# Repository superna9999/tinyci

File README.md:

# TinyCI

General Concept:

TinyCi Main
-----------

Relay board controlled by a `W32-ETH01` module.

Input: 5V

Produced:
- v0.5: x5 produced, x4 soldered, x3 used in production
- v0.7: x5 produced & used in production
- v0.8: Design done

ESP32 Firmware: see `firmware/tinyci-fw/`

Remote Relay Control script: see `firmware/tinyci-fw/tinyci-relay.py`

TinyCi USB
-----------

Secondary Relay board controlled by the `W32-ETH01` on the main board.

Input: 5V to 12V

Produced:
- v0.1: x5 produced, x3 soldered, x2 used in production
- v0.3: x5 Produced, x0 used in production

TinySerial
-----------

Quad FTDI board + breakout of all FTDI I/Os with the TinyCi form factor + holes
to hook a Pi/LaFrite/LePotato to control the FTDI + TinyCi USBs.

Input: USB

Produced:
- v1: x5 Produced, failed to bringup, will be replaced with OctoSerial using CH348Q

LICENCE
-------

```
CERN OPEN HARDWARE LICENCE v1.1
```

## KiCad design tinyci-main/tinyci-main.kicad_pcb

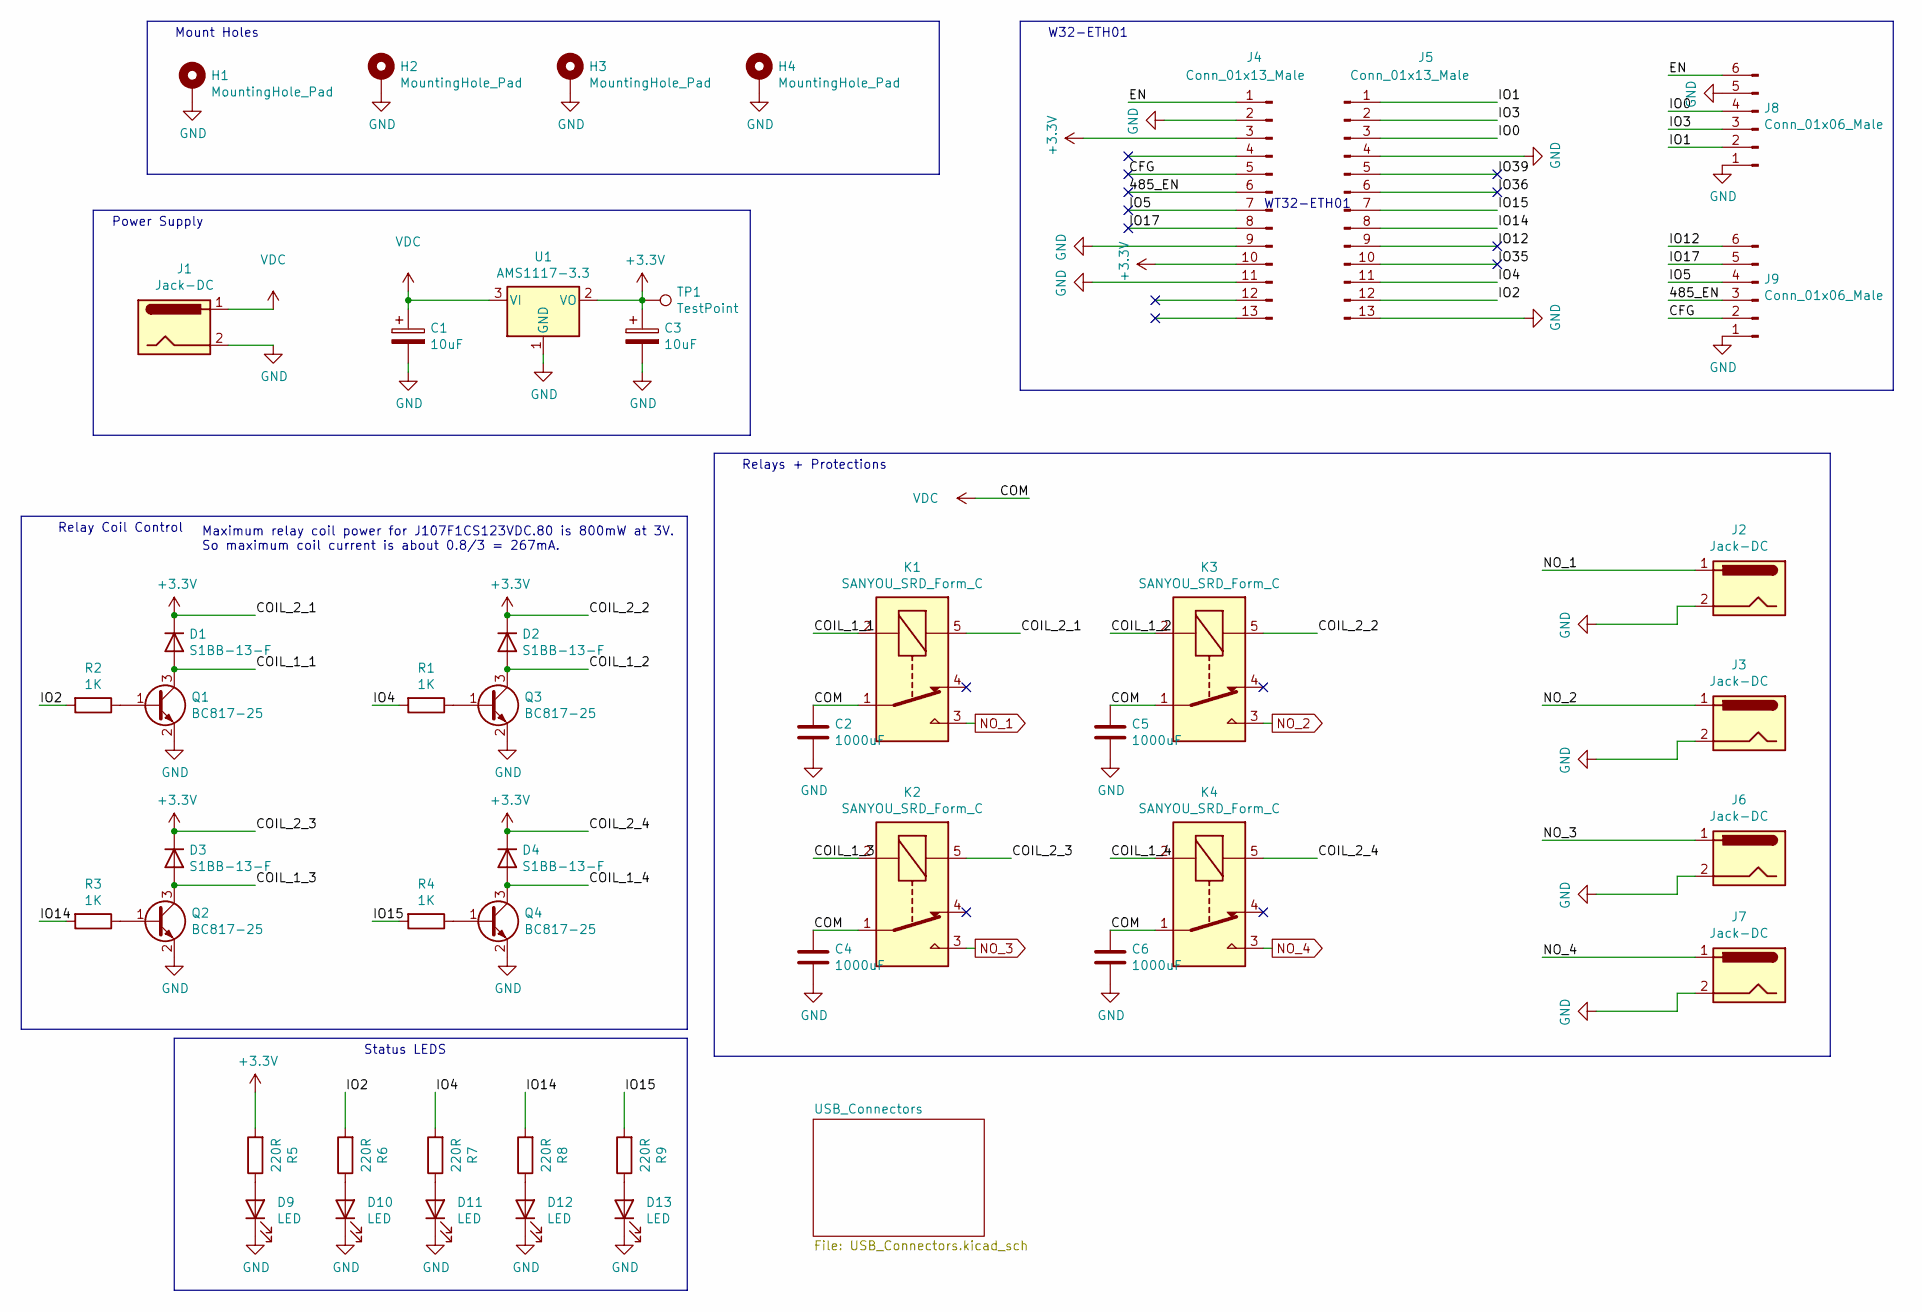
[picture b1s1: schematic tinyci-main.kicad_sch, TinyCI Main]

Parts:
C1, C3: 10uF; CP_EIA-7343-31_Kemet-D
C2, C4, C5, C6: 1000uF; CP_Radial_D10.0mm_P5.00mm
D1, D2, D3, D4: S1BB-13-F; D_SMB_Handsoldering
D9, D10, D11, D12, D13: LED; LED_1206_3216Metric
H1, H2, H3, H4: MountingHole_Pad; MountingHole_3.2mm_M3_Pad
J1, J2, J3, J6, J7: Jack-DC; BarrelJack_Horizontal
J4, J5: Conn_01x13_Male; PinHeader_1x13_P2.54mm_Vertical
J8, J9: Conn_01x06_Male; PinHeader_1x06_P2.54mm_Vertical
K1, K2, K3, K4: SANYOU_SRD_Form_C; Relay_SPDT_SANYOU_SRD_Series_Form_C
Q1, Q2, Q3, Q4: BC817-25; SOT-23
R1, R2, R3, R4: 1K; R_1206_3216Metric
R5, R6, R7, R8, R9: 220R; R_1206_3216Metric
TP1: TestPoint; TestPoint_Pad_D2.0mm
U1: AMS1117-3.3; SOT-223-3_TabPin2

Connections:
+3.3V: C3.1, D1.1 (K), D2.1 (K), D3.1 (K), D4.1 (K), J4.3, J4.10, K1.5, K2.5, K3.5, K4.5, R5.2, TP1.1, U1.2 (VO)
/485_EN: J4.6, J9.3
/CFG: J4.5, J9.2
/COIL_1_1: D1.2 (A), K1.2, Q1.3 (C)
/COIL_1_2: D2.2 (A), K3.2, Q3.3 (C)
/COIL_1_3: D3.2 (A), K2.2, Q2.3 (C)
/COIL_1_4: D4.2 (A), K4.2, Q4.3 (C)
/EN: J4.1, J8.6
/IO0: J5.3, J8.4
/IO1: J5.1, J8.2
/IO2: J5.12, R2.2, R6.2
/IO3: J5.2, J8.3
/IO4: J5.11, R1.2, R7.2
/IO5: J4.7, J9.4
/IO12: J5.9, J9.6
/IO14: J5.8, R3.2, R8.2
/IO15: J5.7, R4.2, R9.2
/IO17: J4.8, J9.5
/IO35: J5.10
/IO36: J5.6
/IO39: J5.5
GND: C1.2, C2.2, C3.2, C4.2, C5.2, C6.2, D9.1 (K), D10.1 (K), D11.1 (K), D12.1 (K), D13.1 (K), H1.1, H2.1, H3.1, H4.1, J1.2, J2.2, J3.2, J4.2, J4.9, J4.11, J5.4, J5.13, J6.2, J7.2, J8.1, J8.5, J9.1, Q1.2 (E), Q2.2 (E), Q3.2 (E), Q4.2 (E), U1.1 (GND); also elsewhere on the board
NO_1: J2.1, K1.3; also elsewhere on the board
NO_2: J3.1, K3.3; also elsewhere on the board
NO_3: J6.1, K2.3; also elsewhere on the board
NO_4: J7.1, K4.3; also elsewhere on the board
unnamed: D9.2 (A), R5.1
unnamed: D10.2 (A), R6.1
unnamed: D11.2 (A), R7.1
unnamed: D12.2 (A), R8.1
unnamed: D13.2 (A), R9.1
unnamed: Q1.1 (B), R2.1
unnamed: Q2.1 (B), R3.1
unnamed: Q3.1 (B), R1.1
unnamed: Q4.1 (B), R4.1
VDC: C1.1, C2.1, C4.1, C5.1, C6.1, J1.1, K1.1, K2.1, K3.1, K4.1, U1.3 (VI)

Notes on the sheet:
Status LEDS
Power Supply
W32-ETH01
Mount Holes
Relays + Protections
Relay Coil Control
WT32-ETH01
Maximum relay coil power for J107F1CS123VDC.80 is 800mW at 3V. So maximum coil current is about 0.8/3 = 267mA.

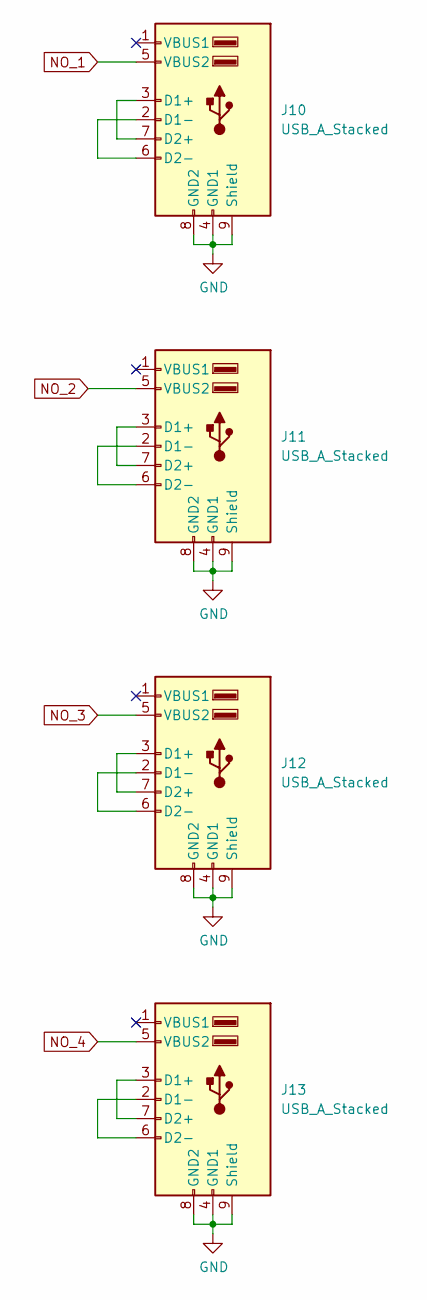
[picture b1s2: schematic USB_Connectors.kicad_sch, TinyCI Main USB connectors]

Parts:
J10, J11, J12, J13: USB_A_Stacked

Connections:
GND: J10.4 (GND1), J10.8 (GND2), J10.9 (Shield), J11.4 (GND1), J11.8 (GND2), J11.9 (Shield), J12.4 (GND1), J12.8 (GND2), J12.9 (Shield), J13.4 (GND1), J13.8 (GND2), J13.9 (Shield); also elsewhere on the board
NO_1: J10.5 (VBUS2); also elsewhere on the board
NO_2: J11.5 (VBUS2); also elsewhere on the board
NO_3: J12.5 (VBUS2); also elsewhere on the board
NO_4: J13.5 (VBUS2); also elsewhere on the board
unnamed: J10.2 (D1-), J10.6 (D2-)
unnamed: J10.3 (D1+), J10.7 (D2+)
unnamed: J11.2 (D1-), J11.6 (D2-)
unnamed: J11.3 (D1+), J11.7 (D2+)
unnamed: J12.2 (D1-), J12.6 (D2-)
unnamed: J12.3 (D1+), J12.7 (D2+)
unnamed: J13.2 (D1-), J13.6 (D2-)
unnamed: J13.3 (D1+), J13.7 (D2+)

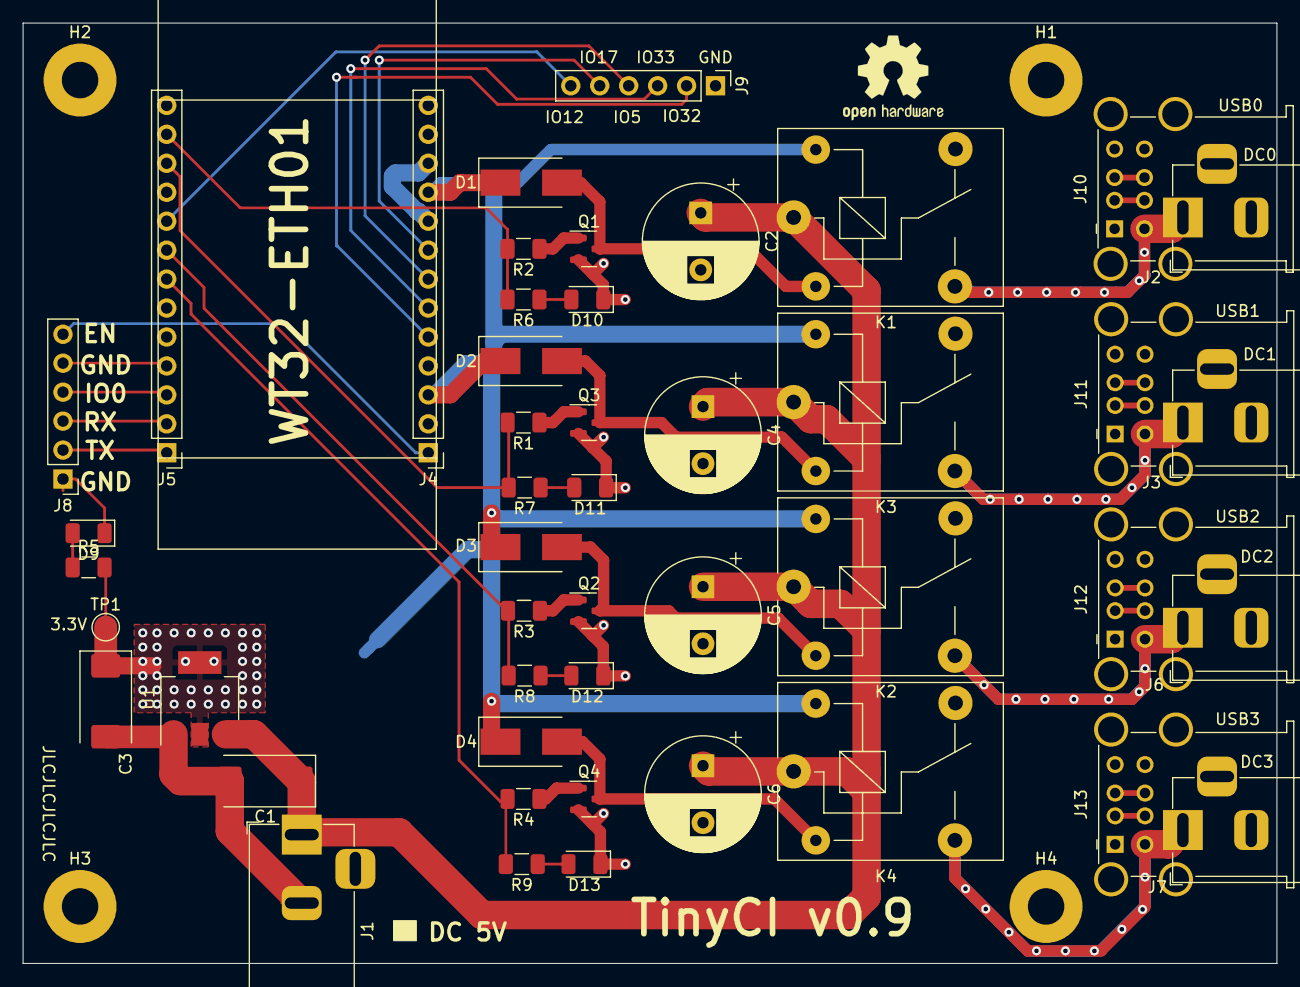
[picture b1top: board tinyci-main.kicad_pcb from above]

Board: 2 copper layers, 110.0 x 82.5 mm, 51 parts (0 on the bottom side), 41 nets.

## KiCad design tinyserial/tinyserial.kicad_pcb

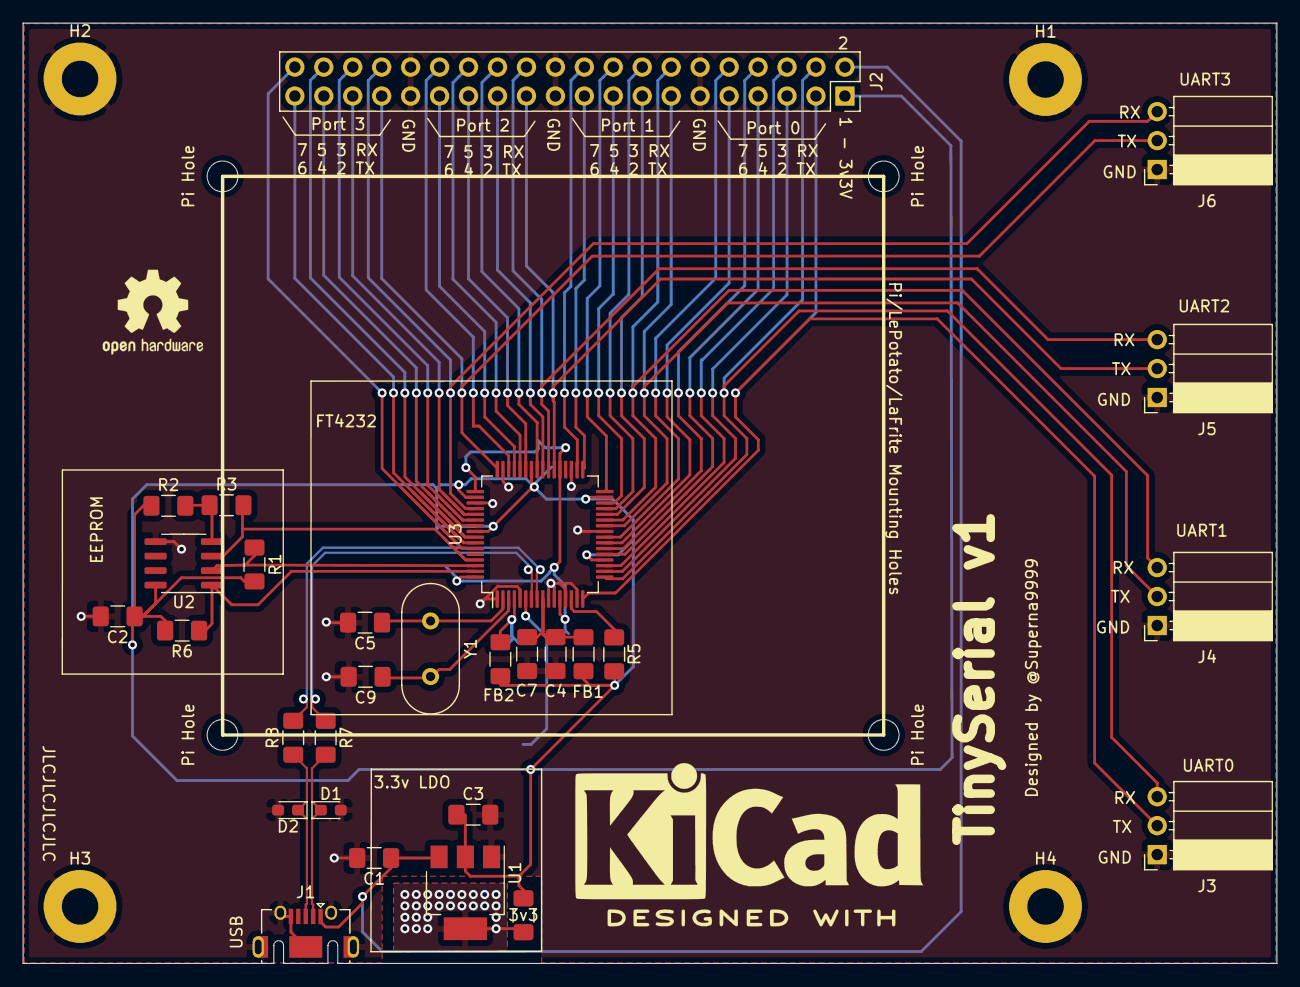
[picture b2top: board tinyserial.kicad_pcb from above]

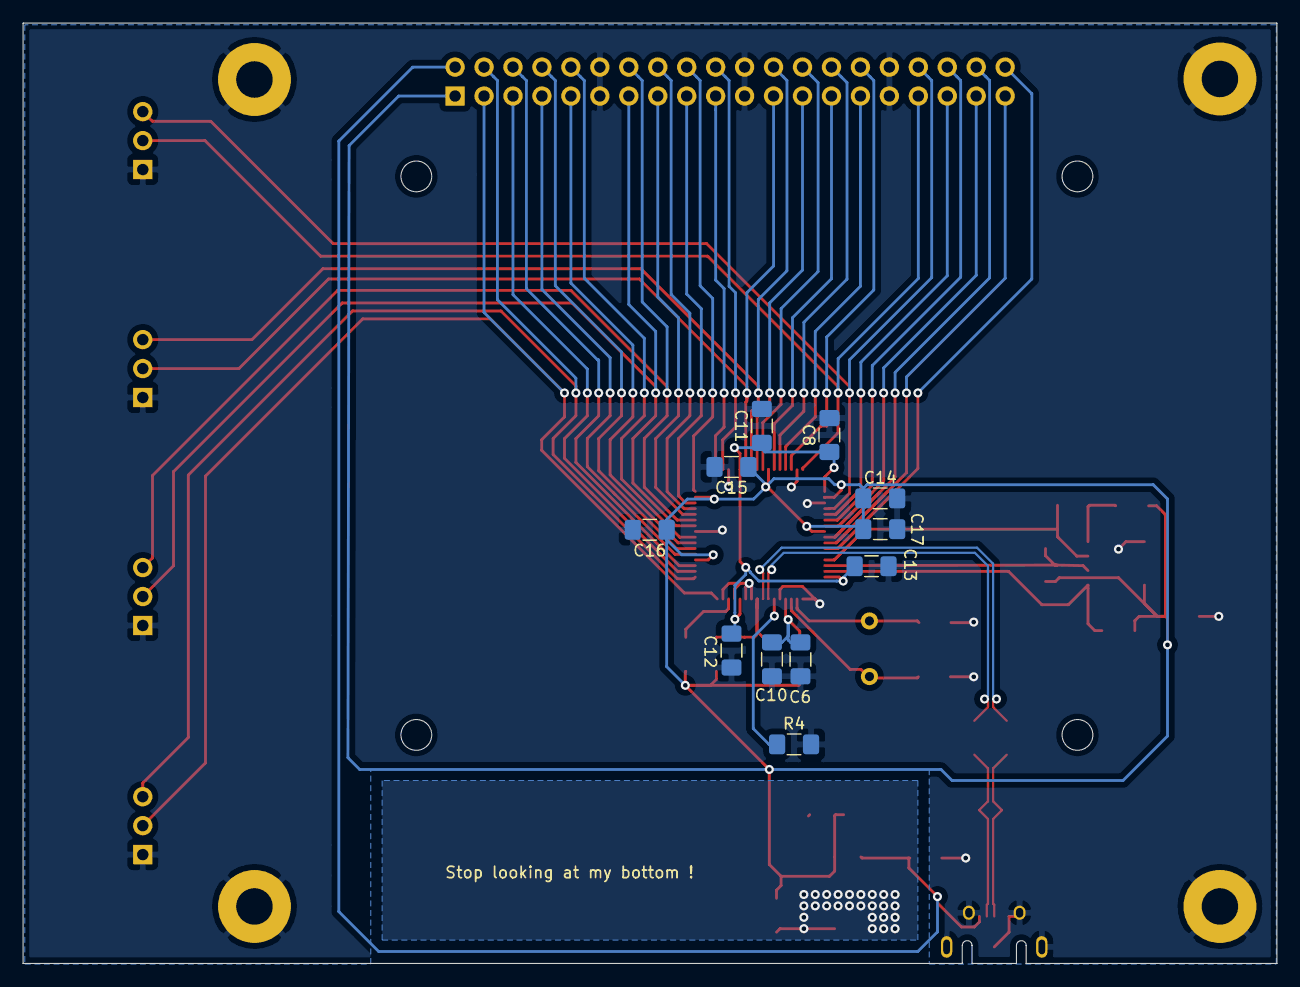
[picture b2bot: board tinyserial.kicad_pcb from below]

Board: 2 copper layers, 110.0 x 82.5 mm, 47 parts (11 on the bottom side), 50 nets.

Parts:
C1, C3: 10uF; C_1206_3216Metric_Pad1.42x1.75mm_HandSolder
C2, C7, C8, C10, C11, C12, C13, C14, C15, C16, C17: 100nF; C_1206_3216Metric_Pad1.42x1.75mm_HandSolder
C4, C6: 4.7uF; C_1206_3216Metric_Pad1.42x1.75mm_HandSolder
C5, C9: 30pF; C_1206_3216Metric_Pad1.42x1.75mm_HandSolder
D1, D2: D_TVS; D_0603_1608Metric_Pad1.05x0.95mm_HandSolder
FB1, FB2: Ferrite_Bead; R_1206_3216Metric_Pad1.42x1.75mm_HandSolder
H1, H2, H3, H4: MountingHole_Pad; MountingHole_3.2mm_M3_Pad
J1: USB_OTG; USB_Micro-AB_Molex_47590-0001
J2: Conn_02x20_Odd_Even; PinSocket_2x20_P2.54mm_Vertical
J3, J4, J5, J6: Conn_01x03_Male; PinSocket_1x03_P2.54mm_Horizontal
Pi Hole: MountingHole_2.7mm_M2.5
Pi Hole#2, Pi Hole#3, Pi Hole#4: MountingHole_2.7mm_M2.5
R1, R2, R6, R7, R8: 10K; R_1206_3216Metric_Pad1.42x1.75mm_HandSolder
R3: 2.2K; R_1206_3216Metric_Pad1.42x1.75mm_HandSolder
R4: 12K/1%; R_1206_3216Metric_Pad1.42x1.75mm_HandSolder
R5: 1K; R_1206_3216Metric_Pad1.42x1.75mm_HandSolder
U1: AMS1117-3.3; SOT-223-3_TabPin2
U2: 93LC46B/SN; SOIC-8_3.9x4.9mm_P1.27mm
U3: FT4232HL; LQFP-64_10x10mm_P0.5mm
Y1: 12MHz; Crystal_HC49-4H_Vertical

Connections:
+1V8: C8.1, C11.1, C12.1, C13.1, U3.12, U3.37, U3.49, U3.64
+3V3: C2.1, C3.1, C14.1, C15.1, C16.1, C17.1, FB1.2, FB2.2, J2.1, R1.2, R2.1, R5.1, R6.2, U1.2, U2.8, U3.20, U3.31, U3.42, U3.50, U3.56
/A2: J2.5, U3.18
/A3: J2.6, U3.19
/A4: J2.7, U3.21
/A5: J2.8, U3.22
/A6: J2.9, U3.23
/A7: J2.10, U3.24
/B2: J2.15, U3.28
/B3: J2.16, U3.29
/B4: J2.17, U3.30
/B5: J2.18, U3.32
/B6: J2.19, U3.33
/B7: J2.20, U3.34
/C2: J2.25, U3.40
/C3: J2.26, U3.41
/C4: J2.27, U3.43
/C5: J2.28, U3.44
/C6: J2.29, U3.45
/C7: J2.30, U3.46
/D2: J2.35, U3.53
/D3: J2.36, U3.54
/D4: J2.37, U3.55
/D5: J2.38, U3.57
/D6: J2.39, U3.58
/D7: J2.40, U3.59
/D+: D2.1, J1.3, R8.1
/D-: D1.1, J1.2, R7.2
/EECLK: R1.1, U2.2, U3.62
/EECS: R6.1, U2.1, U3.63
/EEDATA: R3.2, U2.3, U3.61
/FD+: R8.2, U3.8
/FD-: R7.1, U3.7
/RX0: J2.4, J3.3, U3.17
/RX1: J2.14, J4.3, U3.27
/RX2: J2.24, J5.3, U3.39
/RX3: J2.34, J6.3, U3.52
/TX0: J2.3, J3.2, U3.16
/TX1: J2.13, J4.2, U3.26
/TX2: J2.23, J5.2, U3.38
/TX3: J2.33, J6.2, U3.48
GND: C1.2, C2.2, C3.2, C4.2, C5.2, C6.2, C7.2, C8.2, C9.2, C10.2, C11.2, C12.2, C13.2, C14.2, C15.2, C16.2, C17.2, D1.2, D2.2, H1.1, H2.1, H3.1, H4.1, J1.5, J1.6, J2.11, J2.12, J2.21, J2.22, J2.31, J2.32, J3.1, J4.1, J5.1, J6.1, R4.2, U1.1, U2.5, U3.1, U3.5, U3.10, U3.11, U3.13, U3.15, U3.25, U3.35, U3.47, U3.51
unnamed: C4.1, C7.1, FB1.1, U3.9
unnamed: C5.1, U3.2, Y1.1
unnamed: C9.1, U3.3, Y1.2
unnamed: C6.1, C10.1, FB2.1, U3.4
unnamed: R2.2, R3.1, U2.4
unnamed: R4.1, U3.6
unnamed: R5.2, U3.14
VBUS: C1.1, J1.1, J2.2, U1.3

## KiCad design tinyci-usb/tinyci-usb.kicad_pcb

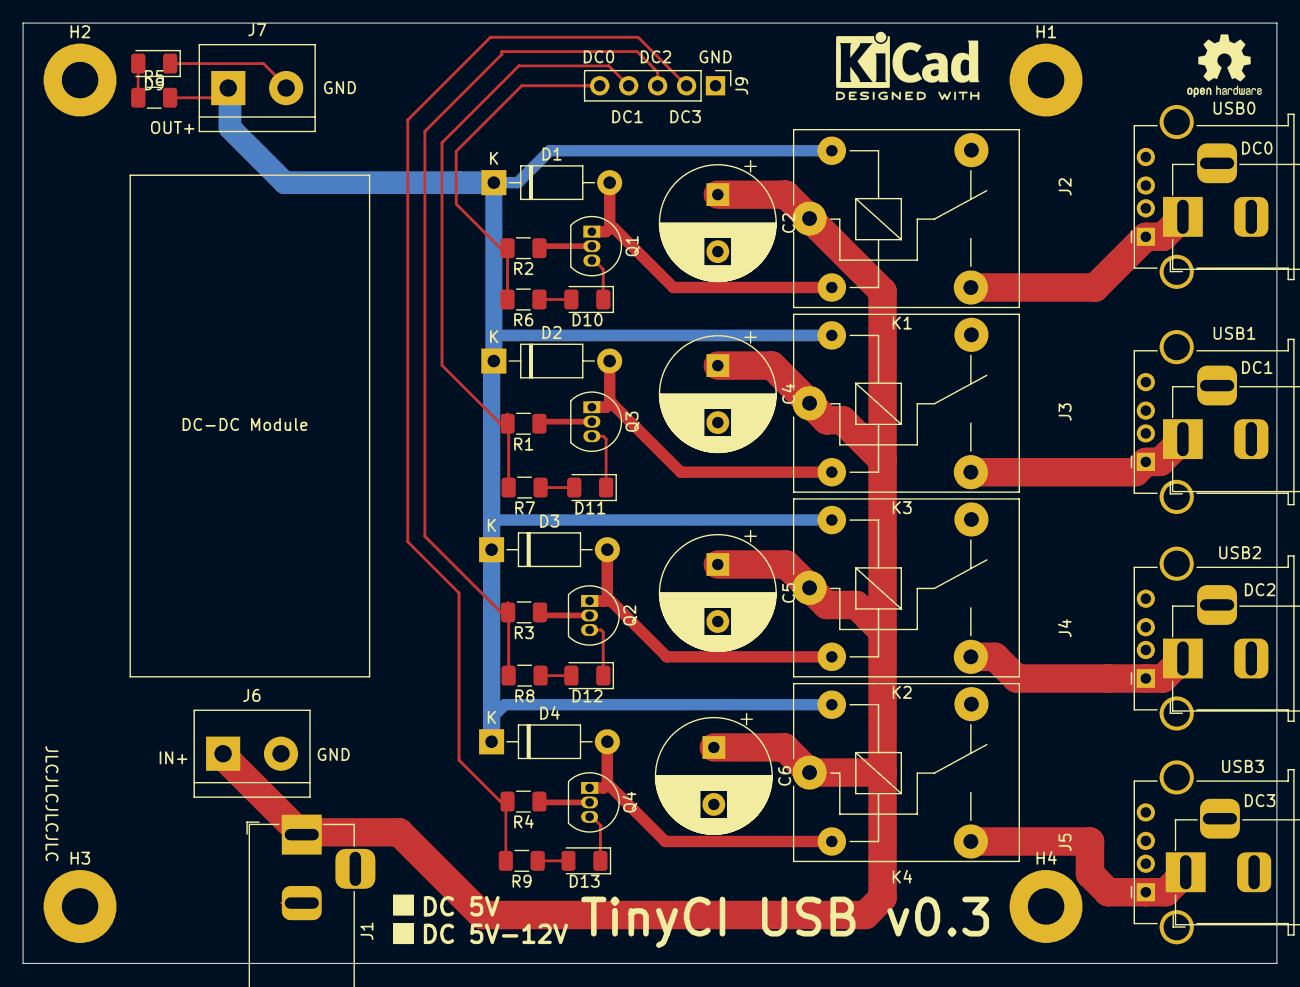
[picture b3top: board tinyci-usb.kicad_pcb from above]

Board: 2 copper layers, 110.0 x 82.5 mm, 46 parts (0 on the bottom side), 24 nets.

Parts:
C2, C4, C5, C6: 1000uF; CP_Radial_D10.0mm_P5.00mm
D1, D2, D3, D4: 1N4001; D_DO-41_SOD81_P10.16mm_Horizontal
D9, D10, D11, D12, D13: LED; LED_1206_3216Metric
H1, H2, H3, H4: MountingHole_Pad; MountingHole_3.2mm_M3_Pad
J1: Jack-DC; BarrelJack_Horizontal
J2, J3, J4, J5: USB_A; USB_A_Stewart_SS-52100-001_Horizontal
J6, J7: Screw_Terminal_01x02; TerminalBlock_bornier-2_P5.08mm
J9: Conn_01x04_Male; PinHeader_1x05_P2.54mm_Vertical
K1, K2, K3, K4: SANYOU_SRD_Form_C; Relay_SPDT_SANYOU_SRD_Series_Form_C
Q1, Q2, Q3, Q4: BC337; TO-92_Inline
R1, R2, R3, R4: 1K; R_1206_3216Metric
R5, R6, R7, R8, R9: 220R; R_1206_3216Metric
USB0, USB1, USB2, USB3: BarrelJack_Horizontal

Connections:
+3V3: D1.1, D2.1, D3.1, D4.1, J7.1, K1.5, K2.5, K3.5, K4.5, R5.2
+VDC: C2.1, C4.1, C5.1, C6.1, J1.1, J6.1, K1.1, K2.1, K3.1, K4.1
/COIL_1_1: D1.2, K1.2, Q1.1
/COIL_1_2: D2.2, K3.2, Q3.1
/COIL_1_3: D3.2, K2.2, Q2.1
/COIL_1_4: D4.2, K4.2, Q4.1
/NO_1: J2.1, K1.3, USB0.1
/NO_2: J3.1, K3.3, USB1.1
/NO_3: J4.1, K2.3, USB2.1
/NO_4: J5.1, K4.3, USB3.1
/RELAY1: J9.5, R2.2, R6.2
/RELAY2: J9.4, R1.2, R7.2
/RELAY3: J9.3, R3.2, R8.2
/RELAY4: J9.2, R4.2, R9.2
GND: C2.2, C4.2, C5.2, C6.2, D9.1, D10.1, D11.1, D12.1, D13.1, H1.1, H2.1, H3.1, H4.1, J1.2, J2.4, J2.5, J3.4, J3.5, J4.4, J4.5, J5.4, J5.5, J6.2, J7.2, J9.1, Q1.3, Q2.3, Q3.3, Q4.3, USB0.2, USB1.2, USB2.2, USB3.2
unnamed: D9.2, R5.1
unnamed: D10.2, R6.1
unnamed: D11.2, R7.1
unnamed: D12.2, R8.1
unnamed: D13.2, R9.1
unnamed: Q1.2, R2.1
unnamed: Q2.2, R3.1
unnamed: Q3.2, R1.1
unnamed: Q4.2, R4.1

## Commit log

2020-11-18 Add v0.4 of tinicy-main and v0.1 of tiny-usb
2020-11-18 Specify Licence
2020-11-18 fixup! Specify Licence
2020-11-18 Version v0.5
2020-11-18 fixup! Version v0.5
2020-11-18 fixup! fixup! Version v0.5
2020-11-18 TinyCI USB v0.1
2020-11-18 Add README and pictures
2020-11-18 fixup! Add README and pictures
2020-11-18 Fixup gitignore
2020-11-18 Add LICENCE to TinyCI-main
2020-11-18 Add LICENCE to TinyCI-USB
2020-11-23 Update prices with aliexpress commands & refs
2020-12-01 Ordered Version !
2020-12-02 Initial version of UDP controlled WT32-ETH01 firmware
2020-12-02 Add UDP command parsing to toggle GPIOs
2021-01-08 TinyCI USB 0.2
    - Updated schematic with correct USB Type A footprint
    - Fixed bad relay output (outputs must be disabled by default, activating the relay will send power to outputs)
    - removed LDO
    - added DC-DC screw terminal footprint + drawing of LM2596 DC-DC module to solder
    - grow mounting hole to 3.2mm to target M3 screws
    - relay 4 was missing Vinput signal to pin 1
2021-01-08 TinyCI 0.6
    - Fixed bad relay output (outputs must be disabled by default, activating the relay will send power to outputs)
    - grow mounting hole to 3.2mm to target M3 screws
    - removed "5v-12v" text, this board will be 5V only, LDO heats too much at 12V
2021-09-03 Add tinyci-relay.py
2021-09-03 Fixup tinyci-relay.py for python3
2021-11-19 TinyCI Main v0.7
    Remove post-relay protections, and move 1000uF caps before relay.
    Add proper OSHW & Made with KiCad logo
2021-11-19 TinyCI USB 0.3
    Remove post-relay protections, and move 1000uF caps before relay.
    Add proper OSHW & Made with KiCad logo
2021-11-19 Introduce TinySerial v1
    FT4232 quad uart board with 40pin header for all I/Os
    with same form factor as TinyCI.
    Also has holes to hook a Pi/LaFrite/LePotato to control the board
    and eventually some TinyCi USB relays.
2022-11-11 firmware: tinyci-relay: remove unused import
    Some import are useless, remove them.
2022-11-11 firmware: tinyci-relay: add a shebang
    Add missing shebang
2022-12-01 tinyci-main: Converted project and schematic to KiCad 6.
    Had to replace C1 and C3 capacitors symbol because it has been renamed in KiCad 6.
2022-12-01 tinyci-main: Converted PCB to KiCad 6.
2022-12-01 tinyci-main: Added stacked USB-A connectors to schematic so they are easier to route.
2022-12-01 tinyci-main: Replaced the PCB single USB-A connectors by the stacked ones.
2022-12-02 tinyci-main: Bumped version to 0.8.
2022-12-02 Update README for TinySerial
2023-01-09 tinyci-relay: need to import sys
    My cleaning via f256e9216f3e ("firmware: tinyci-relay: remove unused import") was too much, I removed sys when I should not.
2023-01-09 convert to new API
    esp_eth_set_default_handlers was removed, so let's convert to new API.
2023-01-09 implement version
    Add a simple VERSION command returning build version
2023-02-15 tinyci-main: Replaced the relay coil flyback diodes by SMD parts to speed up the board assembly.
2023-02-15 tinyci-main: Replaced the relay coil transistors by SMD parts to speed up the board assembly.
2023-02-15 tinyci-main: Bumped version to 0.9.

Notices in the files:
tinyci-main/USB_Connectors.kicad_sch:
Copyright (C) 2021 Neil Armstrong
